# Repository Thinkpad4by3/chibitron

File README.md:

# chibitron
Chibitron is a Electrostatic CRT driver design built to solve the issues I've had with many of the other designs seen elsewhere on the internet. 

## Goals of the Project
* Fully Open Source HW/FW
* Compatible with as many CRTs as possible, as small as a 1EP1 or as big as a 7JP4.
* Single supply 12V input, with all necessary voltages generated on board.
* Onboard vector generation ability
* Ability to play Oscilloscope music with no extra equipment required.
* Built out of entirely currently stocked parts, using more common parts, when possible.

## Design of the system
Design of the system is designed around a two-part architecture. The main board provides all the required voltages to run the tube, mainly A2/A3/Focus control. This provides the main power for the electron gun, and can be adjusted from 400 - 2000V on mono-accelerator tubes (A2), or optionally boosted with another 400-2000V on post-deflection accelerator tubes(A2+A3). Total combined acceleration maxes out at 4kV which is sufficient for a very bright, very sharp image even on the most demanding of tubes. Filament voltage is supplied through a fully isolated 6.3V source, and focus is derived off A2 through a class-A amplfier. 

The 2nd board is the deflection board, which consists of all the required components to take any sort of vector control X/Y signal and amplify it to the +/- 150V required to move the beam around. This board is compatible with almost every type of ES-CRT, including single ended deflection type tubes. All plates are driven by 300Vpk-pk 500KHz bandwidth amplifiers, where gain/offset can be used to control picture size, and neutral voltage can set for astigmatism. Amplifiers are of a class-AB variety, and are closed loop for minimal distortion, and are powered by their own local bi-polar power supplies. 

Z-axis control is currently a WIP, but is going to be fully DC coupled. 

Currently, system has been tested with over a dozen CRTs, all showing clear and bright pictures with excellent clarity and brilliance. Tubes can be swapped in and out quickly with only minor tweaks to the board trimmer potentiometers. 

## CRT terminology:
Electrostatic CRT: Type of cathode-ray tube that uses capacitive plates to steer an electron beam with electric field instead of magnetic field  
H (Heater): Heater, used to heat cathode and cause thermionic emission of electrons  
K (Cathode): Cathode of tube, creates free electrons  
G1 (Grid): Grid control voltage, negatively biased from cathode to control electron beam current (and therefore beam brightness)  
A1 (Focus): Focus control voltage, used to create an electron lens, focusing beam to tight point on the screen surface  
A2 (Accelerator): Main anode for accelerating electrons towards screen   
Dx (Deflection): Plates numbered 1-4 for deflecting beam in X-Y direction. 1-2 are pair, 3-4 pair, with 3-4 usually being the more sensitive pair  
    -some tubes tie D1/D3/A2 together, known as single-ended deflection  
Astigmatism: generated through an offset between Dx neutral voltage and the A2 voltage.  
A3 (Post-deflection Accelerator): Anode inside the bell of the CRT which will accelerate electrons further after deflection. Used for increasing brightness without affecting deflection sensitivity.  

Phosphor: coating on the front of the tube that glows when struck with electrons. Comes in many varieties and colors; most commonly, green.   

Tube types: many US-made tubes follow a very simple naming scheme. For example, the 3BP1.  

3 -> 3" display  
B -> tube series (successor to 3AP1)  
P1 -> P1 phosphor designation, being a green medium persistence type.  

## Current files:
High Voltage supplies:
- main_supply: 1st generation 1000V
- main_supply_2: 1st generation 1500V + FILTERED
- main_supply_3: 2nd generation 2kV + 2kV 
- main_supply_3_revised: 2nd generation 2kV + 2kV BUG FIXED

Deflection:
- deflection_board: 1st generation ANALOG
- deflection_board_2: 2nd generation ANALOG
- deflection_board_3: 3rd generation DIGITAL 
- deflection_board_4: 3rd generation ANALOG
- deflection_board_5: 4th generation ANALOG + COMPOSITE

Check out the README under each folder for more information on the individual. 

## Currently tested working tubes:
3ASPx
3BPx
3JPx
3FPx
3RPx
5BPx
5UPx
5DEPx
5" unknown DuMont rectangular, medium base.
5XPx-B
7VPx

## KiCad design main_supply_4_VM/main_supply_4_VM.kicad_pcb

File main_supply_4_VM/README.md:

## CRT High Voltage Gen.2 

## Status
- Completed, succeeded by main_supply_3_revised
- I would not recommend building this board

##  Design & Architecture 
The architecture was re-thought out from scratch over the previous supply. With the LM5180, they tended to work quite well, however they did have a bit of a major downside....regulation. Under extremely light load, the voltage would soar, and under very heavy load or it would tend to compensate by increasing the output voltage. Given the method of regulation is feedback sensing through the primary side, and high ratio step-up transformers are known for poor leakage inductance, the sensing ability of the converter could be quite poor at times. (See notes on Gen.1 V2 for more info on this)

(Mention the lack of a good method of adjustment due to the Rfb being a single resistor)

The new design uses an LM5155 and a far more conventional topology. The filament was powered through a TL431 regulated isolated flyback converter, and the A2/A3 generation was done through non-isolated ground referenced converters. A2 was referenced to ground, so the A2 supply generated the cathode potential at -400 - 2000V, and A3 was just the positive copy of A2. The main HV supplies use the NA5920-ALD, the only >1:10 ratio transformer available at the moment that is 

1) easily available
2) supports a >1000V HiPOT rating.

You might ask how I planned on getting 2000V out of a (barely) 1000V transformer. Well I'm going to use a voltage multiplier to just multiply the output by 3X. Seems like a good idea....cockroft-walton multipliers have been a proven choice of high-voltage generation for nearly a century. Well, we will get back to this in a bit. The exact topology follows the "boost mode style" found in a few LiDAR supplies and the like, which means that the charge pump caps are seperate from the filter caps, and the filter caps are larger. Otherwise, it operates the same way. Rough calculations say that 3x multiplier @ 2000V should keep the primary side at ~700V even at max voltage, should be fine for a 1500Vrms rated transformer. Primary side spiking thanks to the large 1:24 ratio would be kept at a meager 30V which would allow the choice of some more common low-voltage FETs.

Focus Amplifier was a somewhat odd design. As found on previous designs, the standard focus ladder stack was limiting for larger tubes. The highest voltage potentiometer easily available is 500V, and some larger tubes (7JP/7VP series) takes nearly 1kV on A1.

Revised from the LM5180, now uses the LM5155

designed to be SSR regulated, which was for better performance

higher voltage, more power

focus amplfiier was cursed, but it did work & iso-amp

moving the controls to the primary side for safety. 

opto feedback stuff 

NA5920-ALD transformer

## Troubleshooting & Bring-up 
lol SO MANY PROBLEMS

reversed problem with the opto-isolator.

missing soft-start

improperly UVLO spec'd resistors

- [ ] Wrong value resistors for the feedback chain for 400-2.1kV - A2
- [ ] Increase soft-start capacitance
- [ ] Transformer wrong: switch to Wurth 10:1 part
- [ ] MOSFET too low voltage: need >200V part
- [ ] Fix layout to not have GND overlapping underneath transformer
- [ ] Add RC filtering to A2,A3 + LC filtering to Filament
- [ ] Change TLV314 to TLV237, check >6.8V operation
- [ ] Fix the 20 ohm resistors in the VM’s to be in the correct spot
- [ ] Add soft start to filament supply 
- [ ] Capacitively couple feedback -> test this (only on A3)
- [ ] Change the RC filtering?? 2/2n + 100ohm & 1k R slope comp.
- [ ] Change connectors and remove focus amp from power supply side.
- [ ] Re-layout and silkscreen
- [ ] Add large input cap and filtering 
- [x] UVLO resistors configured incorrectly to disable on low-voltage - 10k lower
- [x] Fix diode on filament to be Schottky not HV rectifier
- [x] Add 220n + 2k resistor on A2
- [x] Add interlock if no power to op amp -> no A2 supply?
- [x] ADD POWER TO THE FUCKING AMPLIFIER FOR A2 FEEDBACK
- [x] Wrong sense resistor values for Current sense - 0.02ohm
- [x] Wrong value resistors for the feedback chain for 400-2.1kV - A3
- [x] Opto feedback wired up wrong - fix

## Learnings
really need to revisit how amplifiers works 

need to severely filter my output 

flybacks have sort of unregulated voltage

amp design seems good, continue with. 

8pF = slow feedback. will continue to monitor.

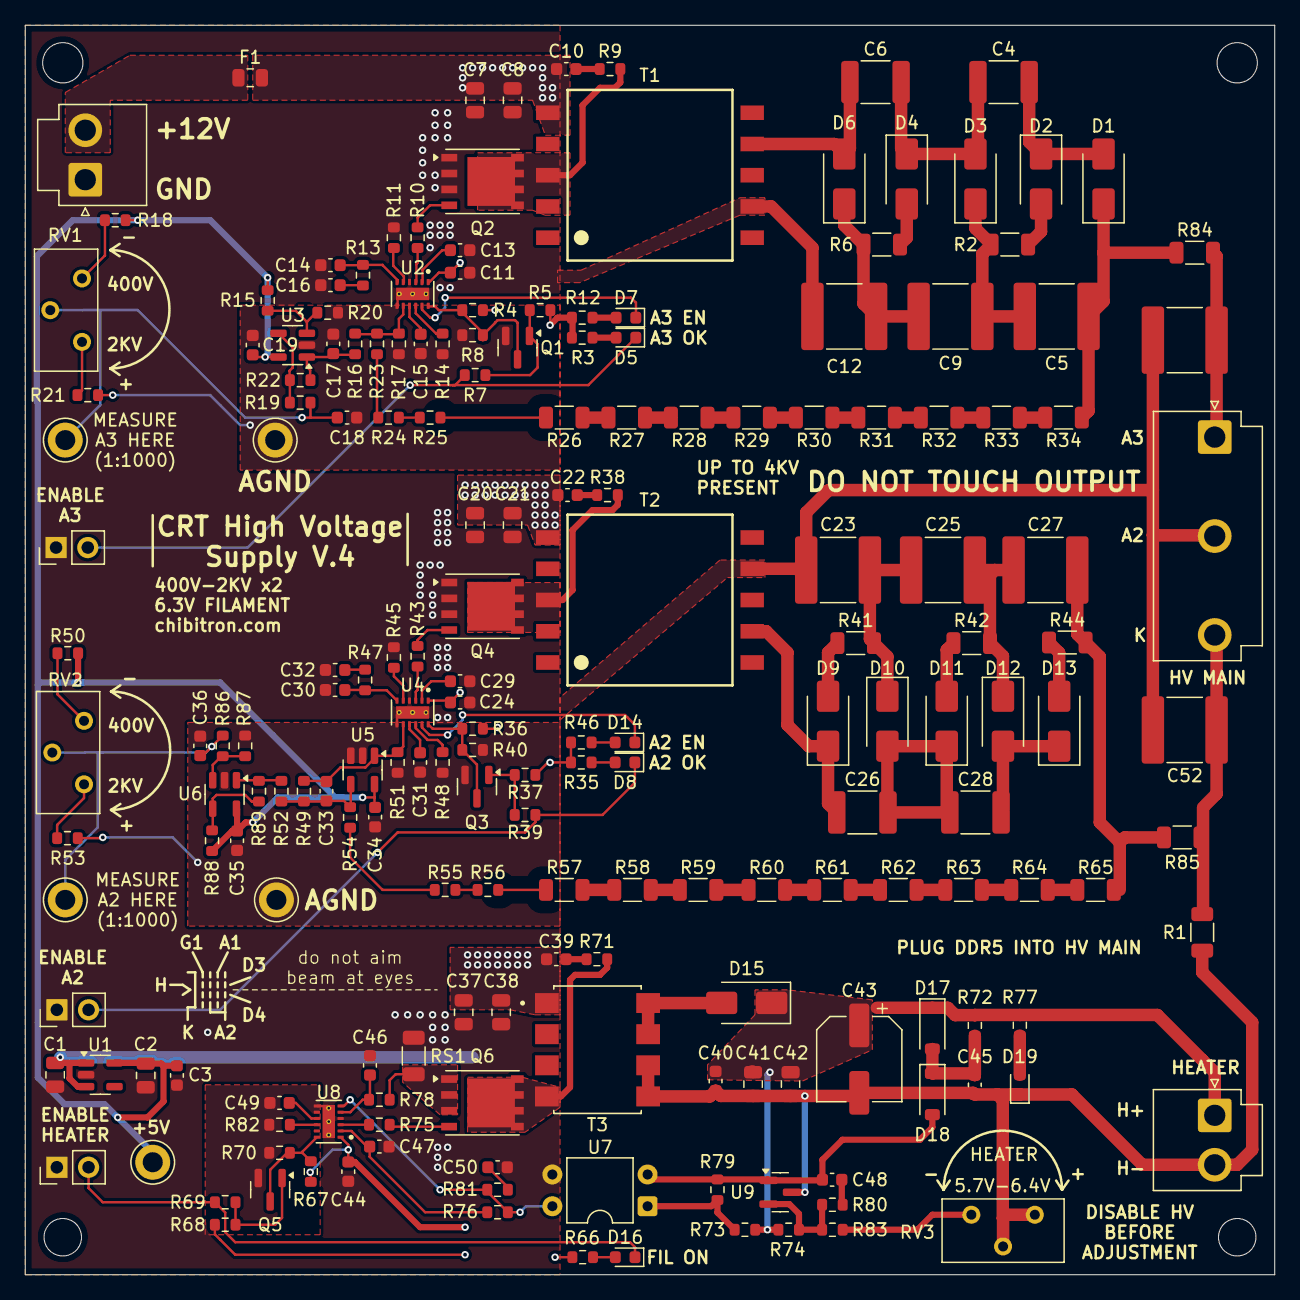
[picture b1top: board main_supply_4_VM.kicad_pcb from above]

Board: 2 copper layers, 100.0 x 100.0 mm, 197 parts (0 on the bottom side), 120 nets.

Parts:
C1, C2, C7, C8, C20, C21, C37, C38, C41, C42: 10u; C_0805_2012Metric
C3, C11, C19, C24, C34, C35, C40, C44: 100n; C_0603_1608Metric
C4, C6, C26, C28: 100n; C_1812_4532Metric
C5, C9, C12, C23, C25, C27: 220n; C_2220_5750Metric
C10, C22, C39: 220p; C_0603_1608Metric
C13, C29, C47: 1u; C_0603_1608Metric
C14, C17, C18, C30, C36: 100p; C_0603_1608Metric
C15, C31, C49: 47n; C_0603_1608Metric
C16, C32: 470n; C_0603_1608Metric
C33: 20p; C_0603_1608Metric
C43: 100u; CP_Elec_6.3x7.7
C45: 4.7u; C_0603_1608Metric
C46: 470p; C_0603_1608Metric
C48, C50: 220n; C_0603_1608Metric
C51, C52: 10n; C_2220_5750Metric
D1, D2, D3, D4, D6, D9, D10, D11, D12, D13: D; D_SMA
D5, D7, D8, D14, D16, D19: LED; LED_0603_1608Metric
D15: D_Schottky; D_SMA
D17, D18: D_Schottky; D_SOD-123
F1: Fuse; Fuse_0805_2012Metric
J1: 12V IN; JST_VH_B2P-VH-B_1x02_P3.96mm_Vertical
J2: A3_EN; PinHeader_1x02_P2.54mm_Vertical
J3: A2_EN; PinHeader_1x02_P2.54mm_Vertical
J4: FIL_EN; PinHeader_1x02_P2.54mm_Vertical
J5: MAIN HV; JST_VH_B3P5-VH-B_1x05_P3.96mm_Vertical
J6: FILAMENT; JST_VH_B2P-VH-B_1x02_P3.96mm_Vertical
NT1, NT2, NT3: NetTie_2; NetTie_0.2mm
Q1, Q3, Q5: 2N7002; SOT-23
Q2, Q4, Q6: Si7450DP; PowerPAK_SO-8_Single
R1, R26, R27, R28, R29, R30, R31, R32, R33, R34, R57, R58, R59, R60, R61, R62, R63, R64, R65: 1Meg; R_1206_3216Metric
R2, R6, R41, R42, R44: 20; R_1206_3216Metric
R3, R12, R35, R66: 39k; R_0603_1608Metric
R4, R36, R67, R82: 50k; R_0603_1608Metric
R5, R37, R68, R72: 100k; R_0603_1608Metric
R7, R13, R39, R47, R73, R79, R80, R81: 1k; R_0603_1608Metric
R8, R11, R16, R17, R19, R22, R40, R45, R52, R69, R70: 10k; R_0603_1608Metric
R9, R38, R71: 100; R_0603_1608Metric
R10, R43, R75: 0; R_0603_1608Metric
R14, R48: 220k; R_0603_1608Metric
R15: 12k; R_0603_1608Metric
R18, R50: 18.7k; R_0603_1608Metric
R20, R87, R88: 3k; R_0603_1608Metric
R21, R53: 2.49k; R_0603_1608Metric
R23, R24, R25, R54, R55, R56: 330k; R_0603_1608Metric
R46, R77: 22k; R_0603_1608Metric
R49: 25k; R_0603_1608Metric
R51: 4.7k; R_0603_1608Metric
R74: 33k; R_0603_1608Metric
R76: 5k; R_0603_1608Metric
R78: 20; R_0603_1608Metric
R83: 21k; R_0603_1608Metric
R84, R85: 1.5k; R_1206_3216Metric
R86, R89: 240; R_0603_1608Metric
RS1: 0.02; R_1206_3216Metric
RV1, RV2: 10k; Potentiometer_Bourns_3296Y_Vertical
RV3: 4.7k; Potentiometer_Bourns_3296Y_Vertical
T1, T2: 750315839; WE-FLYLT_EP13_5465
T3: YA9033-ALD; XFMR_YA9033-ALD
TP1: A3-ADJ; TestPoint_Keystone_5010-5014_Multipurpose
TP2: A2-ADJ; TestPoint_Keystone_5010-5014_Multipurpose
TP3: AGND3; TestPoint_Keystone_5010-5014_Multipurpose
TP4: AGND; TestPoint_Keystone_5010-5014_Multipurpose
TP5: 5V; TestPoint_Keystone_5010-5014_Multipurpose
U1: AP2204K-5.0; SOT-23-5
U2, U4, U8: LM5155DSSR; IC_LM5155DSSR
U3, U5, U6: TLV314QDBVR; SOT-23-5
U7: PC817; DIP-4_W7.62mm
U9: TL431DBZ; SOT-23

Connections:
+5V: C2.1, C3.1, C19.1, C34.1, C35.1, R15.1, R18.1, R50.1, R88.2, TP5.1, U1.5 (VOUT), U3.5 (V+), U5.5 (V+), U6.5 (V+)
+12V: C1.1, C7.1, C8.1, C10.1, C11.1, C20.1, C21.1, C22.1, C24.1, C37.1, C38.1, C39.1, C44.1, F1.2, R3.1, R4.1, R5.2, R12.1, R35.1, R36.1, R37.2, R46.1, R66.1, R67.1, R68.2, T1.5, T2.5, T3.1, U1.1 (VIN), U1.3 (EN), U2.1 (BIAS), U4.1 (BIAS), U8.1 (BIAS)
/12V_IN: F1.1, J1.2
/A2 Supply/-2KV: C52.1, J5.5, R1.1, R85.2
/A2 Supply/A2_FB: C27.2, R44.2, R65.1, R85.1
/A2 Supply/EN: D8.1 (K), J3.2, R39.1
/A2 Supply/FB_HV: C33.1, R49.1, R51.1, U4.8 (FB), U5.1
/A2 Supply/FB_HV_LADDER: C33.2, R49.2, R52.1, R54.2, U5.4 (-)
/A2 Supply/GATE_DRAIN: Q4.5 (D), R38.2, T2.3
/A2 Supply/PGOOD_HV: D14.1 (K), U4.11 (PGOOD)
/A2 Supply/UVLO: Q3.3 (D), R36.2, R40.1, U4.12 (UVLO/EN/SYNC)
/A2 Supply/VCC: C29.1, U4.2 (VCC)
/A3 Supply/+PDA: C51.1, J5.1, R84.2
/A3 Supply/EN: D5.1 (K), J2.2, R7.1
/A3 Supply/FB_PDA: R16.2, R17.2, R23.2, U2.8 (FB)
/A3 Supply/GATE_DRAIN: Q2.5 (D), R9.2, T1.3
/A3 Supply/OUTPUT_ADJ: C17.1, R16.1, R22.1, U3.1
/A3 Supply/PDA_FB: C5.2, D1.1 (K), R34.1, R84.1
/A3 Supply/PGOOD_HV: D7.1 (K), U2.11 (PGOOD)
/A3 Supply/UVLO: Q1.3 (D), R4.2, R8.1, U2.12 (UVLO/EN/SYNC)
/A3 Supply/VCC: C13.1, U2.2 (VCC)
/Filament Supply/CATHODE: C40.2, C41.2, C42.2, C43.2, C45.2, D19.1 (K), J6.2, R1.2, RV3.1, RV3.2, T3.5, T3.6, U9.3 (A)
/Filament Supply/COMP_FB_FIL: R76.2, R81.1, U7.4, U8.6 (COMP)
/Filament Supply/CS_FIL: C46.1, R78.1, U8.5 (CS)
/Filament Supply/EN: D16.1 (K), J4.2, R69.1
/Filament Supply/FILAMENT: C40.1, C41.1, C42.1, C43.1, D15.1 (K), D17.1 (K), J6.1, R72.1, R73.1, R74.1, R77.1
/Filament Supply/MOS_DRAIN_FIL: Q6.5 (D), R71.2, T3.4
/Filament Supply/MOS_SOURCE_FIL: Q6.1 (S), Q6.2 (S), Q6.3 (S), R78.2, RS1.1
/Filament Supply/UVLO: Q5.3 (D), R67.2, R70.1, U8.12 (UVLO/EN/SYNC)
/Filament Supply/VCC_FIL: C47.1, R76.1, U8.2 (VCC)
AGND: C31.2, C34.2, C35.2, C36.2, NT2.1, Q3.2 (S), R40.2, R48.2, R51.2, R53.2, R87.1, TP4.1, U4.7 (AGND), U5.2 (V-), U5.3 (+), U6.2 (V-)
AGND2: C49.2, NT3.1, Q5.2 (S), R70.2, R82.2, U8.7 (AGND), U8.8 (FB)
AGND3: C15.2, C17.2, C18.2, C19.2, NT1.1, Q1.2 (S), R8.2, R14.2, R17.1, R20.2, R21.2, TP3.1, U2.7 (AGND), U3.2 (V-)
GND: C1.2, C2.2, C3.2, C7.2, C8.2, C11.2, C12.1, C13.2, C14.2, C16.2, C20.2, C21.2, C23.1, C24.2, C29.2, C30.2, C32.2, C37.2, C38.2, C44.2, C46.2, C47.2, C50.2, C51.2, C52.2, J1.1, J2.1, J3.1, J4.1, J5.3, NT1.2, NT2.2, NT3.2, Q2.1 (S), Q2.2 (S), Q2.3 (S), Q4.1 (S), Q4.2 (S), Q4.3 (S), R11.2, R45.2, RS1.2, T1.9, T2.7, U1.2 (GND), U2.4 (PGND), U2.13 (EP), U4.4 (PGND), U4.13 (EP), U7.3, U8.4 (PGND), U8.13 (EP)
unnamed: C10.2, R9.1
unnamed: C16.1, R13.2
unnamed: C18.1, R19.2, RV1.2, TP1.1
unnamed: C22.2, R38.1
unnamed: C32.1, R47.2
unnamed: C36.1, R86.1, RV2.2, TP2.1
unnamed: C39.2, R71.1
unnamed: C48.2, R80.1
unnamed: C50.1, R81.2
unnamed: C4.2, D1.2 (A), D2.1 (K)
unnamed: D2.2 (A), R2.2
unnamed: C4.1, C6.2, D3.2 (A), D4.1 (K)
unnamed: C5.1, C9.2, D3.1 (K), R2.1
unnamed: D4.2 (A), R6.2
unnamed: D5.2 (A), R3.2
unnamed: C6.1, D6.2 (A), T1.7
unnamed: C9.1, C12.2, D6.1 (K), R6.1
unnamed: D7.2 (A), R12.2
unnamed: D8.2 (A), R35.2
unnamed: D9.2 (A), R41.1
unnamed: C26.1, D9.1 (K), T2.9
unnamed: C26.2, C28.1, D10.2 (A), D11.1 (K)
unnamed: C23.2, C25.1, D10.1 (K), R41.2
unnamed: D11.2 (A), R42.1
unnamed: C28.2, D12.2 (A), D13.1 (K)
unnamed: C25.2, C27.1, D12.1 (K), R42.2
unnamed: D13.2 (A), R44.1
unnamed: D14.2 (A), R46.2
unnamed: D15.2 (A), T3.7, T3.8
unnamed: D16.2 (A), R66.2
unnamed: C45.1, D17.2 (A), D18.1 (K), R72.2
unnamed: C48.1, D18.2 (A), R79.2, U7.2, U9.1 (K)
unnamed: D19.2 (A), R77.2
unnamed: Q1.1 (G), R5.1, R7.2
unnamed: Q2.4 (G), R10.2
unnamed: Q3.1 (G), R37.1, R39.2
unnamed: Q4.4 (G), R43.2
unnamed: Q5.1 (G), R68.1, R69.2
unnamed: Q6.4 (G), R75.2
unnamed: R18.2, RV1.3
unnamed: R21.1, RV1.1
unnamed: R23.1, R24.2
unnamed: R24.1, R25.2
unnamed: R25.1, R26.2
unnamed: R26.1, R27.2
unnamed: R27.1, R28.2
unnamed: R28.1, R29.2
unnamed: R29.1, R30.2
unnamed: R30.1, R31.2
unnamed: R31.1, R32.2
unnamed: R32.1, R33.2
unnamed: R33.1, R34.2
unnamed: R50.2, RV2.3
unnamed: R52.2, R89.1, U6.1
unnamed: R53.1, RV2.1
unnamed: R54.1, R55.2
unnamed: R55.1, R56.2
unnamed: R56.1, R57.2
unnamed: R57.1, R58.2
unnamed: R58.1, R59.2
unnamed: R59.1, R60.2
unnamed: R60.1, R61.2
unnamed: R61.1, R62.2
unnamed: R62.1, R63.2
unnamed: R63.1, R64.2
unnamed: R64.1, R65.2
unnamed: R73.2, R79.1, U7.1
unnamed: R83.2, RV3.3
unnamed: C14.1, R13.1, U2.6 (COMP)
unnamed: R11.1, U2.5 (CS)
unnamed: R10.1, U2.3 (GATE)
unnamed: R14.1, U2.10 (RT)
unnamed: C15.1, U2.9 (SS)
unnamed: R15.2, R20.1, U3.3 (+)
unnamed: R19.1, R22.2, U3.4 (-)
unnamed: C30.1, R47.1, U4.6 (COMP)
unnamed: R45.1, U4.5 (CS)
unnamed: R43.1, U4.3 (GATE)
unnamed: R48.1, U4.10 (RT)
unnamed: C31.1, U4.9 (SS)
unnamed: R86.2, R87.2, U6.3 (+)
unnamed: R88.1, R89.2, U6.4 (-)
unnamed: R75.1, U8.3 (GATE)
unnamed: R82.1, U8.10 (RT)
unnamed: C49.1, U8.9 (SS)
unnamed: R74.2, R80.2, R83.1, U9.2 (REF)

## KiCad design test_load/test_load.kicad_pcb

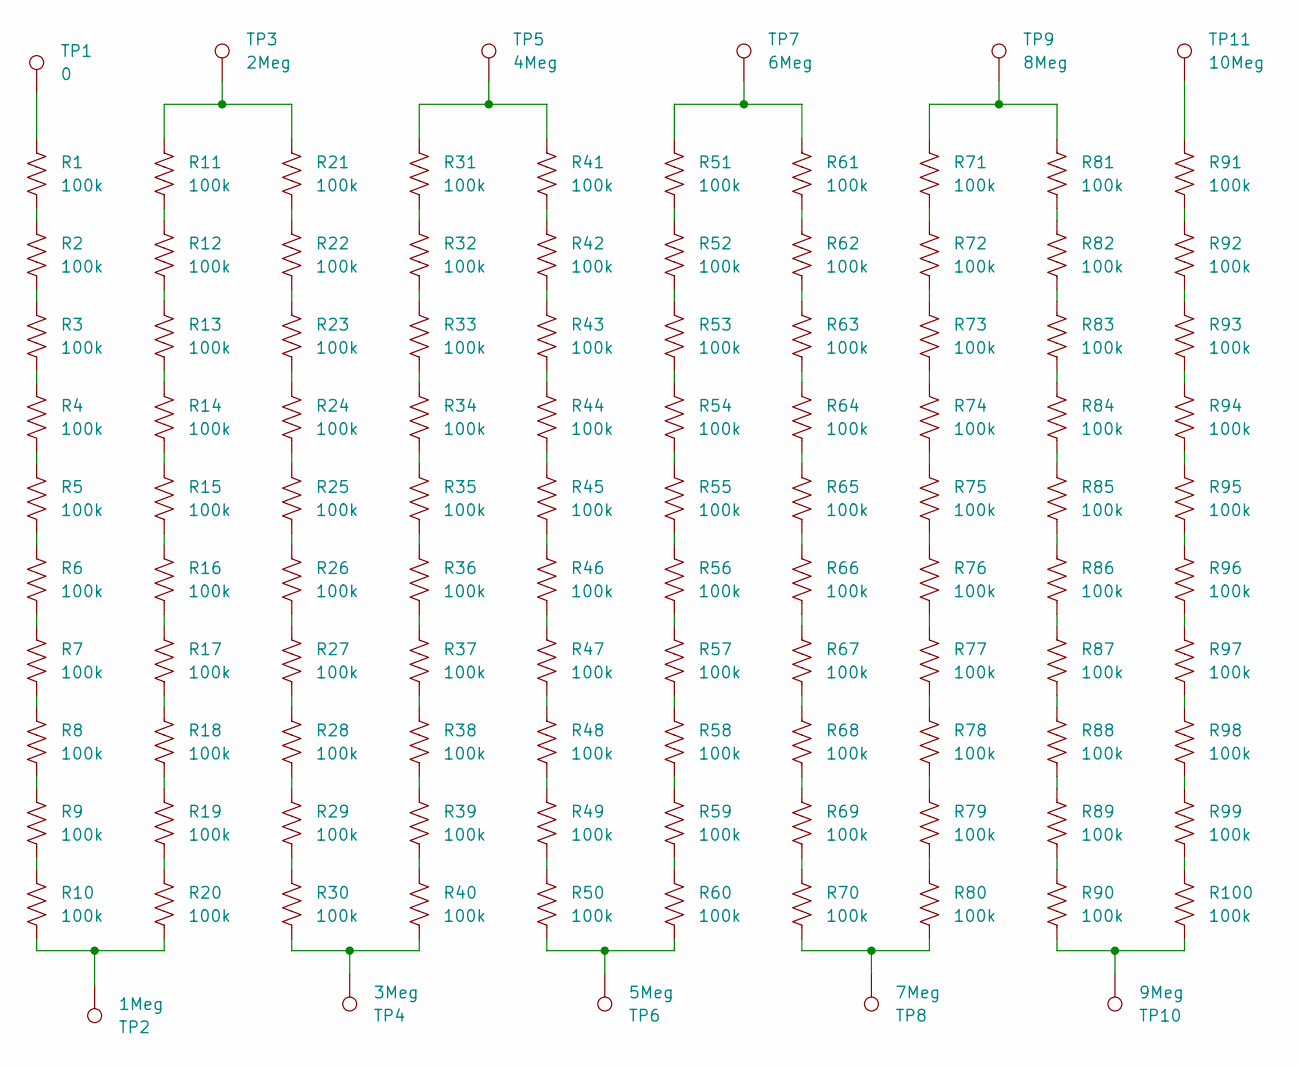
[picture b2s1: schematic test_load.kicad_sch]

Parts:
R1, R2, R3, R4, R5, R6, R7, R8, R9, R10, R11, R12, R13, R14, R15, R16, R17, R18, R19, R20, R21, R22, R23, R24, R25, R26, R27, R28, R29, R30, R31, R32, R33, R34, R35, R36, R37, R38, R39, R40, R41, R42, R43, R44, R45, R46, R47, R48, R49, R50, R51, R52, R53, R54, R55, R56, R57, R58, R59, R60, R61, R62, R63, R64, R65, R66, R67, R68, R69, R70, R71, R72, R73, R74, R75, R76, R77, R78, R79, R80, R81, R82, R83, R84, R85, R86, R87, R88, R89, R90, R91, R92, R93, R94, R95, R96, R97, R98, R99, R100: 100k; R_1206_3216Metric
TP1: 0; TestPoint_Keystone_5010-5014_Multipurpose
TP2: 1Meg; TestPoint_Keystone_5010-5014_Multipurpose
TP3: 2Meg; TestPoint_Keystone_5010-5014_Multipurpose
TP4: 3Meg; TestPoint_Keystone_5010-5014_Multipurpose
TP5: 4Meg; TestPoint_Keystone_5010-5014_Multipurpose
TP6: 5Meg; TestPoint_Keystone_5010-5014_Multipurpose
TP7: 6Meg; TestPoint_Keystone_5010-5014_Multipurpose
TP8: 7Meg; TestPoint_Keystone_5010-5014_Multipurpose
TP9: 8Meg; TestPoint_Keystone_5010-5014_Multipurpose
TP10: 9Meg; TestPoint_Keystone_5010-5014_Multipurpose
TP11: 10Meg; TestPoint_Keystone_5010-5014_Multipurpose

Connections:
unnamed: R1.1, TP1.1
unnamed: R1.2, R2.1
unnamed: R2.2, R3.1
unnamed: R3.2, R4.1
unnamed: R4.2, R5.1
unnamed: R5.2, R6.1
unnamed: R6.2, R7.1
unnamed: R7.2, R8.1
unnamed: R8.2, R9.1
unnamed: R9.2, R10.1
unnamed: R10.2, R20.2, TP2.1
unnamed: R11.1, R21.1, TP3.1
unnamed: R11.2, R12.1
unnamed: R12.2, R13.1
unnamed: R13.2, R14.1
unnamed: R14.2, R15.1
unnamed: R15.2, R16.1
unnamed: R16.2, R17.1
unnamed: R17.2, R18.1
unnamed: R18.2, R19.1
unnamed: R19.2, R20.1
unnamed: R21.2, R22.1
unnamed: R22.2, R23.1
unnamed: R23.2, R24.1
unnamed: R24.2, R25.1
unnamed: R25.2, R26.1
unnamed: R26.2, R27.1
unnamed: R27.2, R28.1
unnamed: R28.2, R29.1
unnamed: R29.2, R30.1
unnamed: R30.2, R40.2, TP4.1
unnamed: R31.1, R41.1, TP5.1
unnamed: R31.2, R32.1
unnamed: R32.2, R33.1
unnamed: R33.2, R34.1
unnamed: R34.2, R35.1
unnamed: R35.2, R36.1
unnamed: R36.2, R37.1
unnamed: R37.2, R38.1
unnamed: R38.2, R39.1
unnamed: R39.2, R40.1
unnamed: R41.2, R42.1
unnamed: R42.2, R43.1
unnamed: R43.2, R44.1
unnamed: R44.2, R45.1
unnamed: R45.2, R46.1
unnamed: R46.2, R47.1
unnamed: R47.2, R48.1
unnamed: R48.2, R49.1
unnamed: R49.2, R50.1
unnamed: R50.2, R60.2, TP6.1
unnamed: R51.1, R61.1, TP7.1
unnamed: R51.2, R52.1
unnamed: R52.2, R53.1
unnamed: R53.2, R54.1
unnamed: R54.2, R55.1
unnamed: R55.2, R56.1
unnamed: R56.2, R57.1
unnamed: R57.2, R58.1
unnamed: R58.2, R59.1
unnamed: R59.2, R60.1
unnamed: R61.2, R62.1
unnamed: R62.2, R63.1
unnamed: R63.2, R64.1
unnamed: R64.2, R65.1
unnamed: R65.2, R66.1
unnamed: R66.2, R67.1
unnamed: R67.2, R68.1
unnamed: R68.2, R69.1
unnamed: R69.2, R70.1
unnamed: R70.2, R80.2, TP8.1
unnamed: R71.1, R81.1, TP9.1
unnamed: R71.2, R72.1
unnamed: R72.2, R73.1
unnamed: R73.2, R74.1
unnamed: R74.2, R75.1
unnamed: R75.2, R76.1
unnamed: R76.2, R77.1
unnamed: R77.2, R78.1
unnamed: R78.2, R79.1
unnamed: R79.2, R80.1
unnamed: R81.2, R82.1
unnamed: R82.2, R83.1
unnamed: R83.2, R84.1
unnamed: R84.2, R85.1
unnamed: R85.2, R86.1
unnamed: R86.2, R87.1
unnamed: R87.2, R88.1
unnamed: R88.2, R89.1
unnamed: R89.2, R90.1
unnamed: R91.1, TP11.1
unnamed: R91.2, R92.1
unnamed: R92.2, R93.1
unnamed: R93.2, R94.1
unnamed: R94.2, R95.1
unnamed: R95.2, R96.1
unnamed: R96.2, R97.1
unnamed: R97.2, R98.1
unnamed: R98.2, R99.1
unnamed: R99.2, R100.1
unnamed: R90.2, R100.2, TP10.1

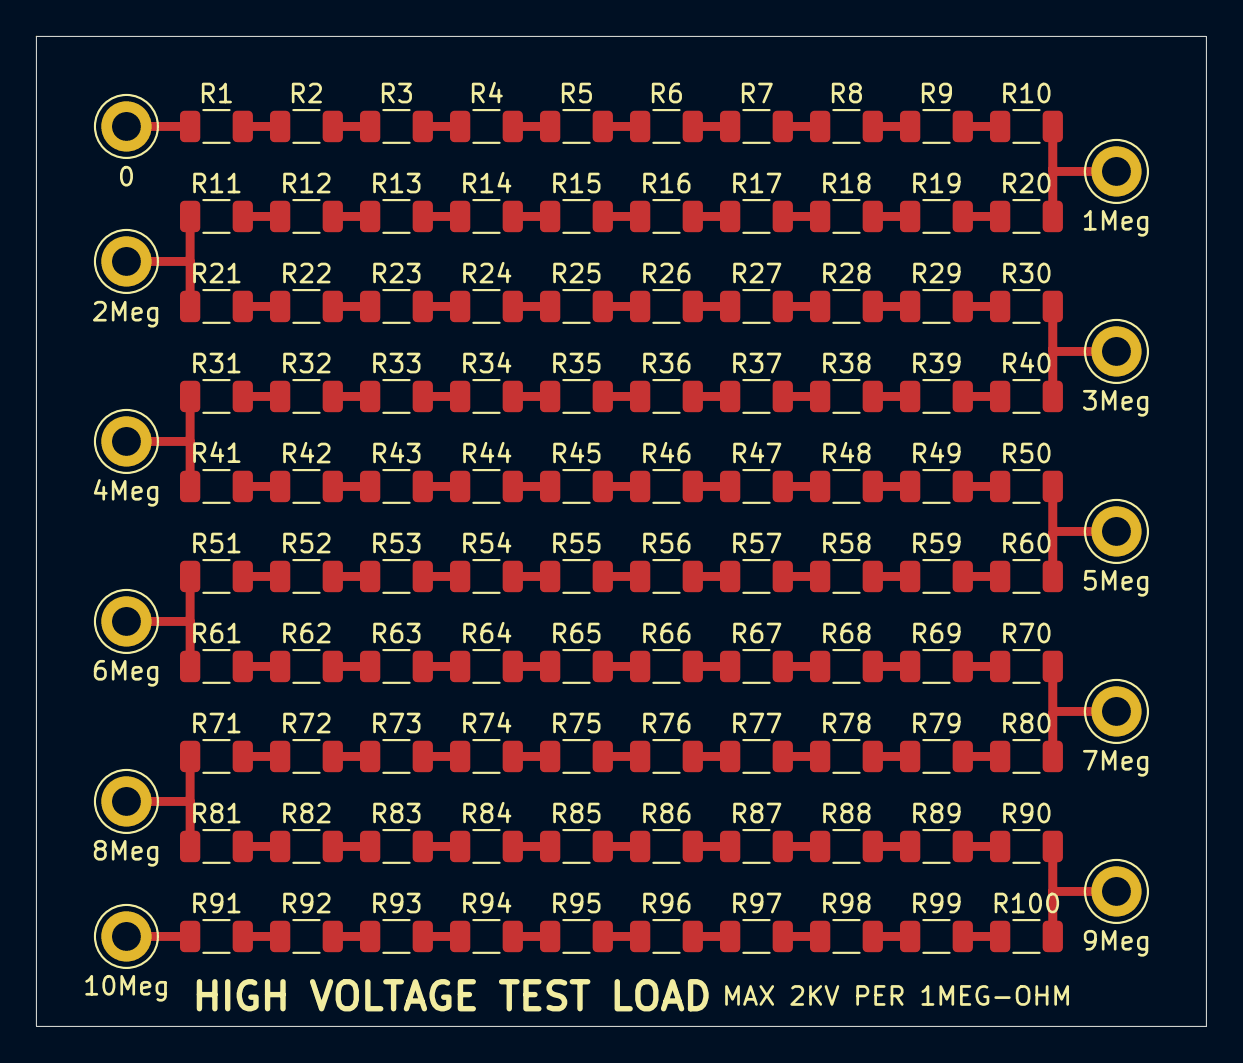
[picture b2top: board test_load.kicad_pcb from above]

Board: 2 copper layers, 65.0 x 55.0 mm, 111 parts (0 on the bottom side), 101 nets.

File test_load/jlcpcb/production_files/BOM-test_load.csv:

Comment,Designator,Footprint,LCSC,Quantity
100k,"R1,R10,R100,R11,R12,R13,R14,R15,R16,R17,R18,R19,R2,R20,R21,R22,R23,R24,R25,R26,R27,R28,R29,R3,R30,R31,R32,R33,R34,R35,R36,R37,R38,R39,R4,R40,R41,R42,R43,R44,R45,R46,R47,R48,R49,R5,R50,R51,R52,R53,R54,R55,R56,R57,R58,R59,R6,R60,R61,R62,R63,R64,R65,R66,R67,R68,R69,R7,R70,R71,R72,R73,R74,R75,R76,R77,R78,R79,R8,R80,R81,R82,R83,R84,R85,R86,R87,R88,R89,R9,R90,R91,R92,R93,R94,R95,R96,R97,R98,R99",R_1206_3216Metric,C17927,100

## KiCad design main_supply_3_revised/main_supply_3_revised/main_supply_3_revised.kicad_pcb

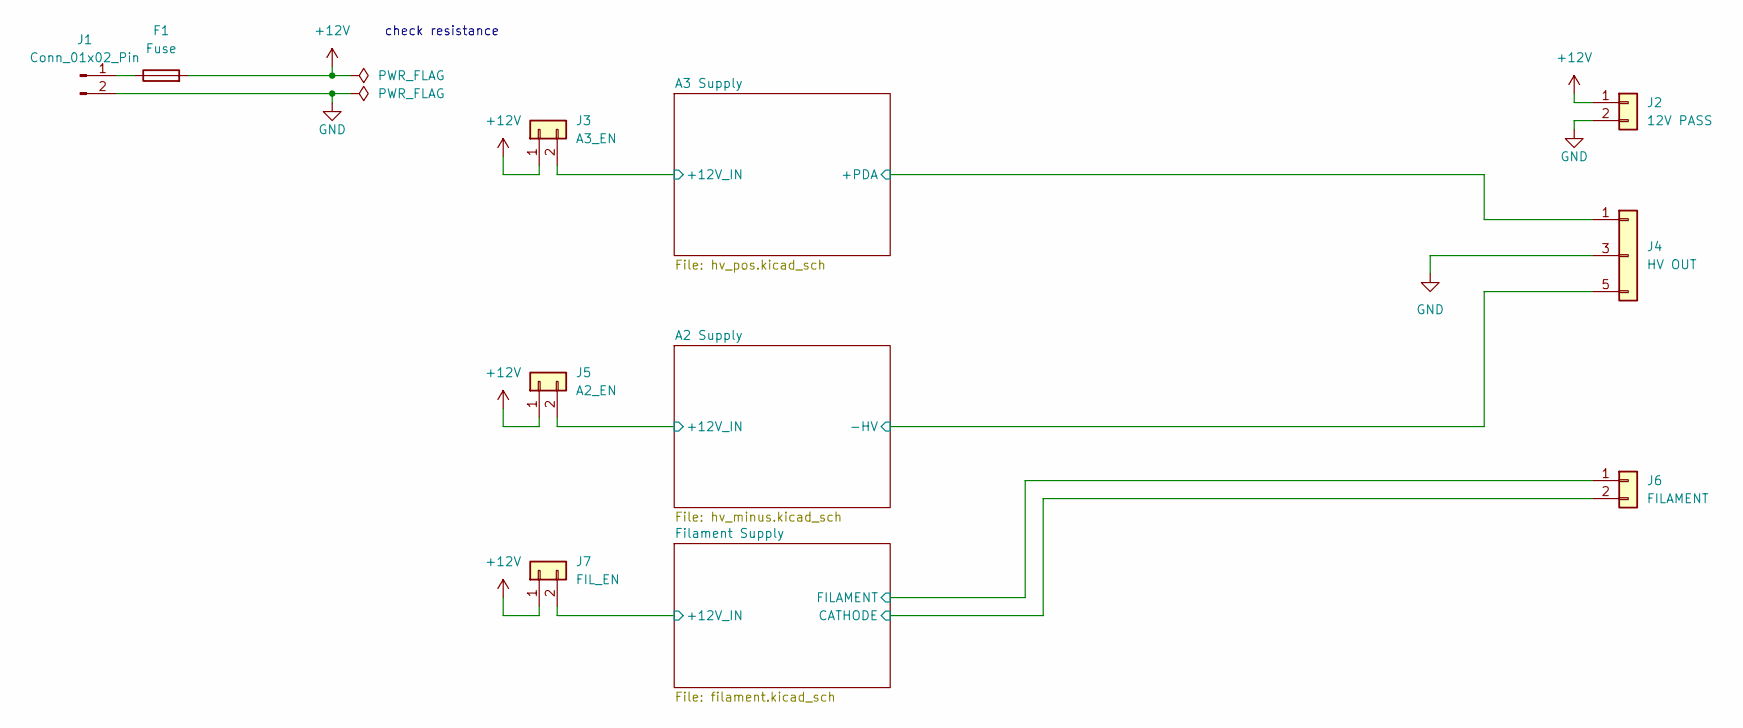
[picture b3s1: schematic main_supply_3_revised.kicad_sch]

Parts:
F1: Fuse; Fuseholder_Littelfuse_Nano2_154x
J1: Conn_01x02_Pin; Molex_KK-396_5273-02A_1x02_P3.96mm_Vertical
J2: 12V PASS
J3: A3_EN; PinHeader_1x02_P2.54mm_Vertical
J4: HV OUT; JST_VH_B5P-VH-B_1x05_P3.96mm_Vertical
J5: A2_EN; PinHeader_1x02_P2.54mm_Vertical
J6: FILAMENT; JST_VH_B2P-VH-B_1x02_P3.96mm_Vertical
J7: FIL_EN; PinHeader_1x02_P2.54mm_Vertical

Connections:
+12V: F1.2, J2.1, J3.1, J5.1, J7.1
/A2 Supply/+12V_IN: J5.2; also elsewhere on the board
/A2 Supply/-HV: J4.5; also elsewhere on the board
/A3 Supply/+12V_IN: J3.2; also elsewhere on the board
/A3 Supply/+PDA: J4.1; also elsewhere on the board
/Filament Supply/+12V_IN: J7.2; also elsewhere on the board
/Filament Supply/CATHODE: J6.2; also elsewhere on the board
/Filament Supply/FILAMENT: J6.1; also elsewhere on the board
GND: J1.2, J2.2, J4.3; also elsewhere on the board
unnamed: F1.1, J1.1

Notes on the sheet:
check resistance

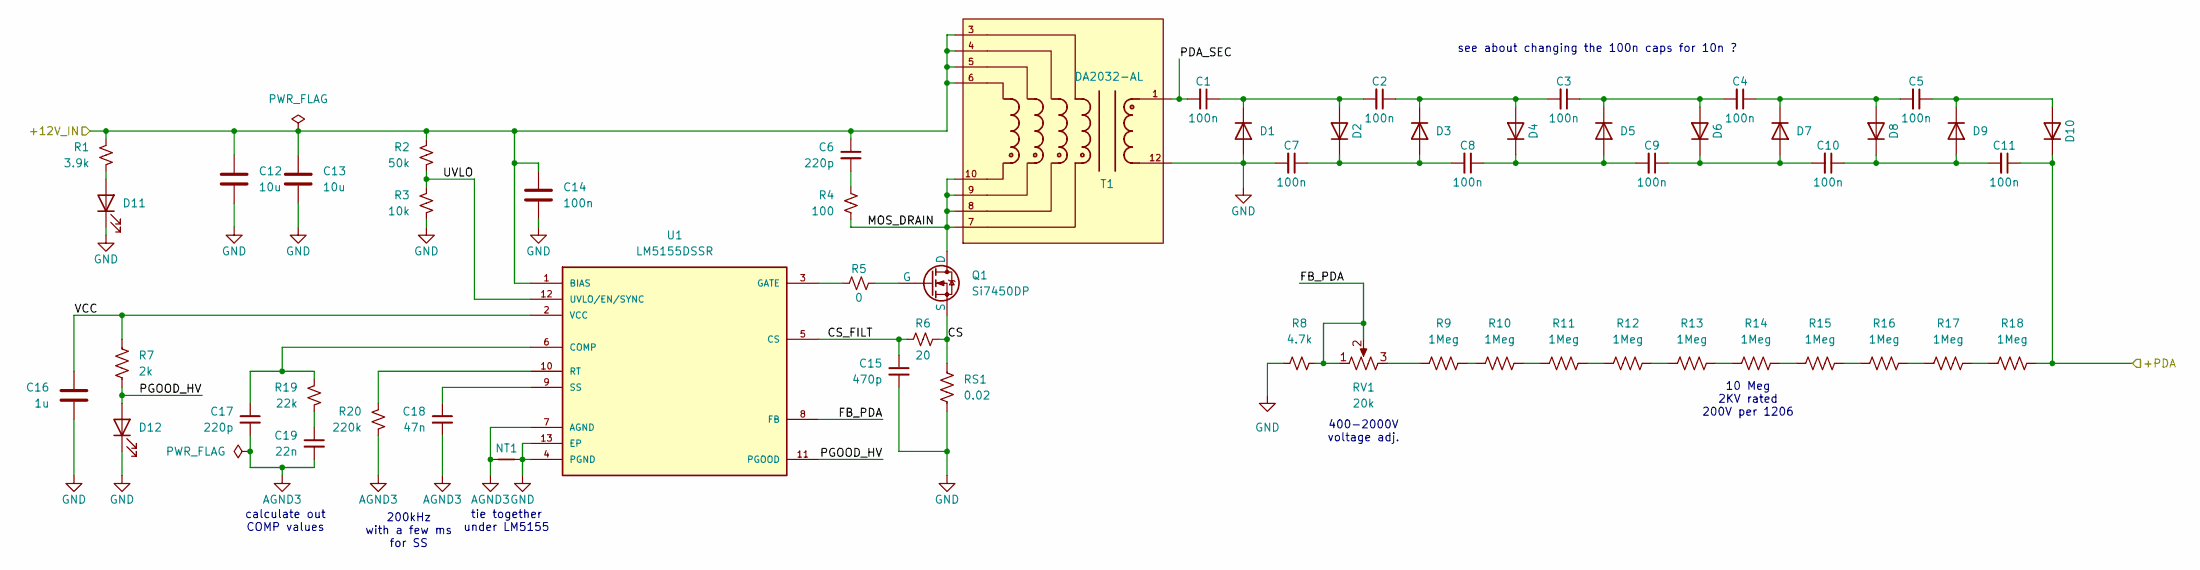
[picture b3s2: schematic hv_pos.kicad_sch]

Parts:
C1, C2, C3, C4, C5, C7, C8, C9, C10, C11: 100n; C_1812_4532Metric
C6: 220p; C_0805_2012Metric
C12, C13: 10u; C_0805_2012Metric
C14: 100n; C_0603_1608Metric
C15: 470p; C_0603_1608Metric
C16: 1u; C_0603_1608Metric
C17: 220p; C_0603_1608Metric
C18: 47n; C_0603_1608Metric
C19: 22n; C_0603_1608Metric
D1, D2, D3, D4, D5, D6, D7, D8, D9, D10: D; D_SMA
D11, D12: LED; LED_0603_1608Metric
NT1: NetTie_2; NetTie-2_SMD_Pad0.5mm
Q1: Si7450DP; PowerPAK_SO-8_Single
R1: 3.9k; R_0603_1608Metric
R2: 50k; R_0603_1608Metric
R3: 10k; R_0603_1608Metric
R4: 100; R_1206_3216Metric
R5: 0; R_0603_1608Metric
R6: 20; R_0603_1608Metric
R7: 2k; R_0603_1608Metric
R8: 4.7k; R_0603_1608Metric
R9, R10, R11, R12, R13, R14, R15, R16, R17, R18: 1Meg; R_1206_3216Metric
R19: 22k; R_0603_1608Metric
R20: 220k; R_0603_1608Metric
RS1: 0.02; R_1206_3216Metric
RV1: 20k; Potentiometer_Bourns_3296Y_Vertical
T1: DA2032-AL
U1: LM5155DSSR; IC_LM5155DSSR; PARTREV E

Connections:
/A3 Supply/+12V_IN: C6.1, C12.1, C13.1, C14.1, R1.1, R2.1, T1.3, T1.4, T1.5, T1.6, U1.1 (BIAS); also elsewhere on the board
/A3 Supply/+PDA: C11.1, D10.1 (K), R18.2; also elsewhere on the board
/A3 Supply/CS: Q1.1 (S), Q1.2 (S), Q1.3 (S), R6.2, RS1.1
/A3 Supply/CS_FILT: C15.1, R6.1, U1.5 (CS)
/A3 Supply/FB_PDA: R8.2, RV1.1, RV1.2, U1.8 (FB)
/A3 Supply/MOS_DRAIN: Q1.5 (D), R4.2, T1.7, T1.8, T1.9, T1.10
/A3 Supply/PDA_SEC: C1.2, T1.1
/A3 Supply/PGOOD_HV: D12.2 (A), R7.2, U1.11 (PGOOD)
/A3 Supply/UVLO: R2.2, R3.1, U1.12 (UVLO/EN/SYNC)
/A3 Supply/VCC: C16.1, R7.1, U1.2 (VCC)
AGND3: C17.2, C18.2, C19.2, NT1.1, R20.2, U1.7 (AGND)
GND: C7.2, C12.2, C13.2, C14.2, C15.2, C16.2, D1.2 (A), D11.1 (K), D12.1 (K), NT1.2, R3.2, R8.1, RS1.2, T1.12, U1.4 (PGND), U1.13 (EP); also elsewhere on the board
unnamed: C6.2, R4.1
unnamed: C19.1, R19.2
unnamed: C1.1, C2.2, D1.1 (K), D2.2 (A)
unnamed: C7.1, C8.2, D2.1 (K), D3.2 (A)
unnamed: C2.1, C3.2, D3.1 (K), D4.2 (A)
unnamed: C8.1, C9.2, D4.1 (K), D5.2 (A)
unnamed: C3.1, C4.2, D5.1 (K), D6.2 (A)
unnamed: C9.1, C10.2, D6.1 (K), D7.2 (A)
unnamed: C4.1, C5.2, D7.1 (K), D8.2 (A)
unnamed: C10.1, C11.2, D8.1 (K), D9.2 (A)
unnamed: C5.1, D9.1 (K), D10.2 (A)
unnamed: D11.2 (A), R1.2
unnamed: Q1.4 (G), R5.2
unnamed: R9.1, RV1.3
unnamed: R9.2, R10.1
unnamed: R10.2, R11.1
unnamed: R11.2, R12.1
unnamed: R12.2, R13.1
unnamed: R13.2, R14.1
unnamed: R14.2, R15.1
unnamed: R15.2, R16.1
unnamed: R16.2, R17.1
unnamed: R17.2, R18.1
unnamed: C17.1, R19.1, U1.6 (COMP)
unnamed: R5.1, U1.3 (GATE)
unnamed: R20.1, U1.10 (RT)
unnamed: C18.1, U1.9 (SS)

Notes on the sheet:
see about changing the 100n caps for 10n ?
400-2000V voltage adj.
calculate out COMP values
10 Meg 2KV rated 200V per 1206
tie together under LM5155
200kHz with a few ms for SS

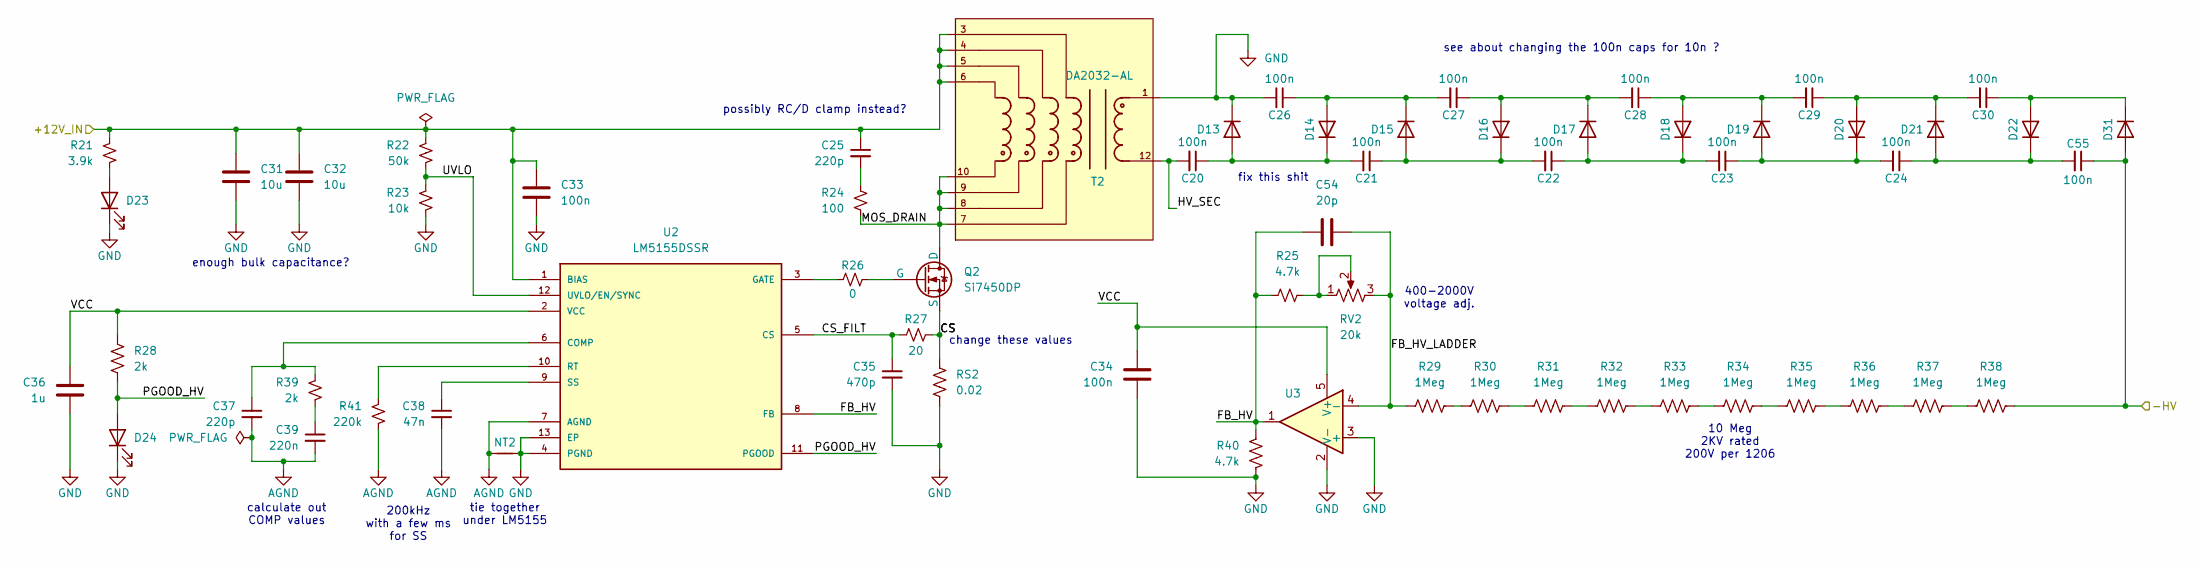
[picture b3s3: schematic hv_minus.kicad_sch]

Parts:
C20, C21, C22, C23, C24, C26, C27, C28, C29, C30, C55: 100n; C_1812_4532Metric
C25: 220p; C_0805_2012Metric
C31, C32: 10u; C_0805_2012Metric
C33, C34: 100n; C_0603_1608Metric
C35: 470p; C_0603_1608Metric
C36: 1u; C_0603_1608Metric
C37: 220p; C_0603_1608Metric
C38: 47n; C_0603_1608Metric
C39: 220n; C_0603_1608Metric
C54: 20p; C_0603_1608Metric
D13, D14, D15, D16, D17, D18, D19, D20, D21, D22, D31: D; D_SMA
D23, D24: LED; LED_0603_1608Metric
NT2: NetTie_2; NetTie-2_SMD_Pad0.5mm
Q2: Si7450DP; PowerPAK_SO-8_Single
R21: 3.9k; R_0603_1608Metric
R22: 50k; R_0603_1608Metric
R23: 10k; R_0603_1608Metric
R24: 100; R_1206_3216Metric
R25, R40: 4.7k; R_0603_1608Metric
R26: 0; R_0603_1608Metric
R27: 20; R_0603_1608Metric
R28, R39: 2k; R_0603_1608Metric
R29, R30, R31, R32, R33, R34, R35, R36, R37, R38: 1Meg; R_1206_3216Metric
R41: 220k; R_0603_1608Metric
RS2: 0.02; R_1206_3216Metric
RV2: 20k; Potentiometer_Bourns_3296Y_Vertical
T2: DA2032-AL
U2: LM5155DSSR; IC_LM5155DSSR; PARTREV E
U3: TLV237; SOT-23-5

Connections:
/A2 Supply/+12V_IN: C25.1, C31.1, C32.1, C33.1, R21.1, R22.1, T2.3, T2.4, T2.5, T2.6, U2.1 (BIAS); also elsewhere on the board
/A2 Supply/-HV: C55.1, D31.2 (A), R38.2; also elsewhere on the board
/A2 Supply/CS: Q2.1 (S), Q2.2 (S), Q2.3 (S), R27.2, RS2.1
/A2 Supply/CS_FILT: C35.1, R27.1, U2.5 (CS)
/A2 Supply/FB_HV: C54.1, R25.1, R40.1, U2.8 (FB), U3.1
/A2 Supply/FB_HV_LADDER: C54.2, R29.1, RV2.3, U3.4 (-)
/A2 Supply/HV_SEC: C20.2, T2.12
/A2 Supply/MOS_DRAIN: Q2.5 (D), R24.2, T2.7, T2.8, T2.9, T2.10
/A2 Supply/PGOOD_HV: D24.2 (A), R28.2, U2.11 (PGOOD)
/A2 Supply/UVLO: R22.2, R23.1, U2.12 (UVLO/EN/SYNC)
/A2 Supply/VCC: C34.1, C36.1, R28.1, U2.2 (VCC), U3.5 (V+)
AGND: C37.2, C38.2, C39.2, NT2.1, R41.2, U2.7 (AGND)
GND: C26.2, C31.2, C32.2, C33.2, C34.2, C35.2, C36.2, D13.1 (K), D23.1 (K), D24.1 (K), NT2.2, R23.2, R40.2, RS2.2, T2.1, U2.4 (PGND), U2.13 (EP), U3.2 (V-), U3.3 (+); also elsewhere on the board
unnamed: C25.2, R24.1
unnamed: C39.1, R39.2
unnamed: C20.1, C21.2, D13.2 (A), D14.1 (K)
unnamed: C26.1, C27.2, D14.2 (A), D15.1 (K)
unnamed: C21.1, C22.2, D15.2 (A), D16.1 (K)
unnamed: C27.1, C28.2, D16.2 (A), D17.1 (K)
unnamed: C22.1, C23.2, D17.2 (A), D18.1 (K)
unnamed: C28.1, C29.2, D18.2 (A), D19.1 (K)
unnamed: C23.1, C24.2, D19.2 (A), D20.1 (K)
unnamed: C29.1, C30.2, D20.2 (A), D21.1 (K)
unnamed: C24.1, C55.2, D21.2 (A), D22.1 (K)
unnamed: C30.1, D22.2 (A), D31.1 (K)
unnamed: D23.2 (A), R21.2
unnamed: Q2.4 (G), R26.2
unnamed: R25.2, RV2.1, RV2.2
unnamed: R29.2, R30.1
unnamed: R30.2, R31.1
unnamed: R31.2, R32.1
unnamed: R32.2, R33.1
unnamed: R33.2, R34.1
unnamed: R34.2, R35.1
unnamed: R35.2, R36.1
unnamed: R36.2, R37.1
unnamed: R37.2, R38.1
unnamed: C37.1, R39.1, U2.6 (COMP)
unnamed: R26.1, U2.3 (GATE)
unnamed: R41.1, U2.10 (RT)
unnamed: C38.1, U2.9 (SS)

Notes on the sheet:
fix this shit
tie together under LM5155
10 Meg 2KV rated 200V per 1206
change these values
400-2000V voltage adj.
200kHz with a few ms for SS
enough bulk capacitance?
calculate out COMP values
see about changing the 100n caps for 10n ?
possibly RC/D clamp instead?
